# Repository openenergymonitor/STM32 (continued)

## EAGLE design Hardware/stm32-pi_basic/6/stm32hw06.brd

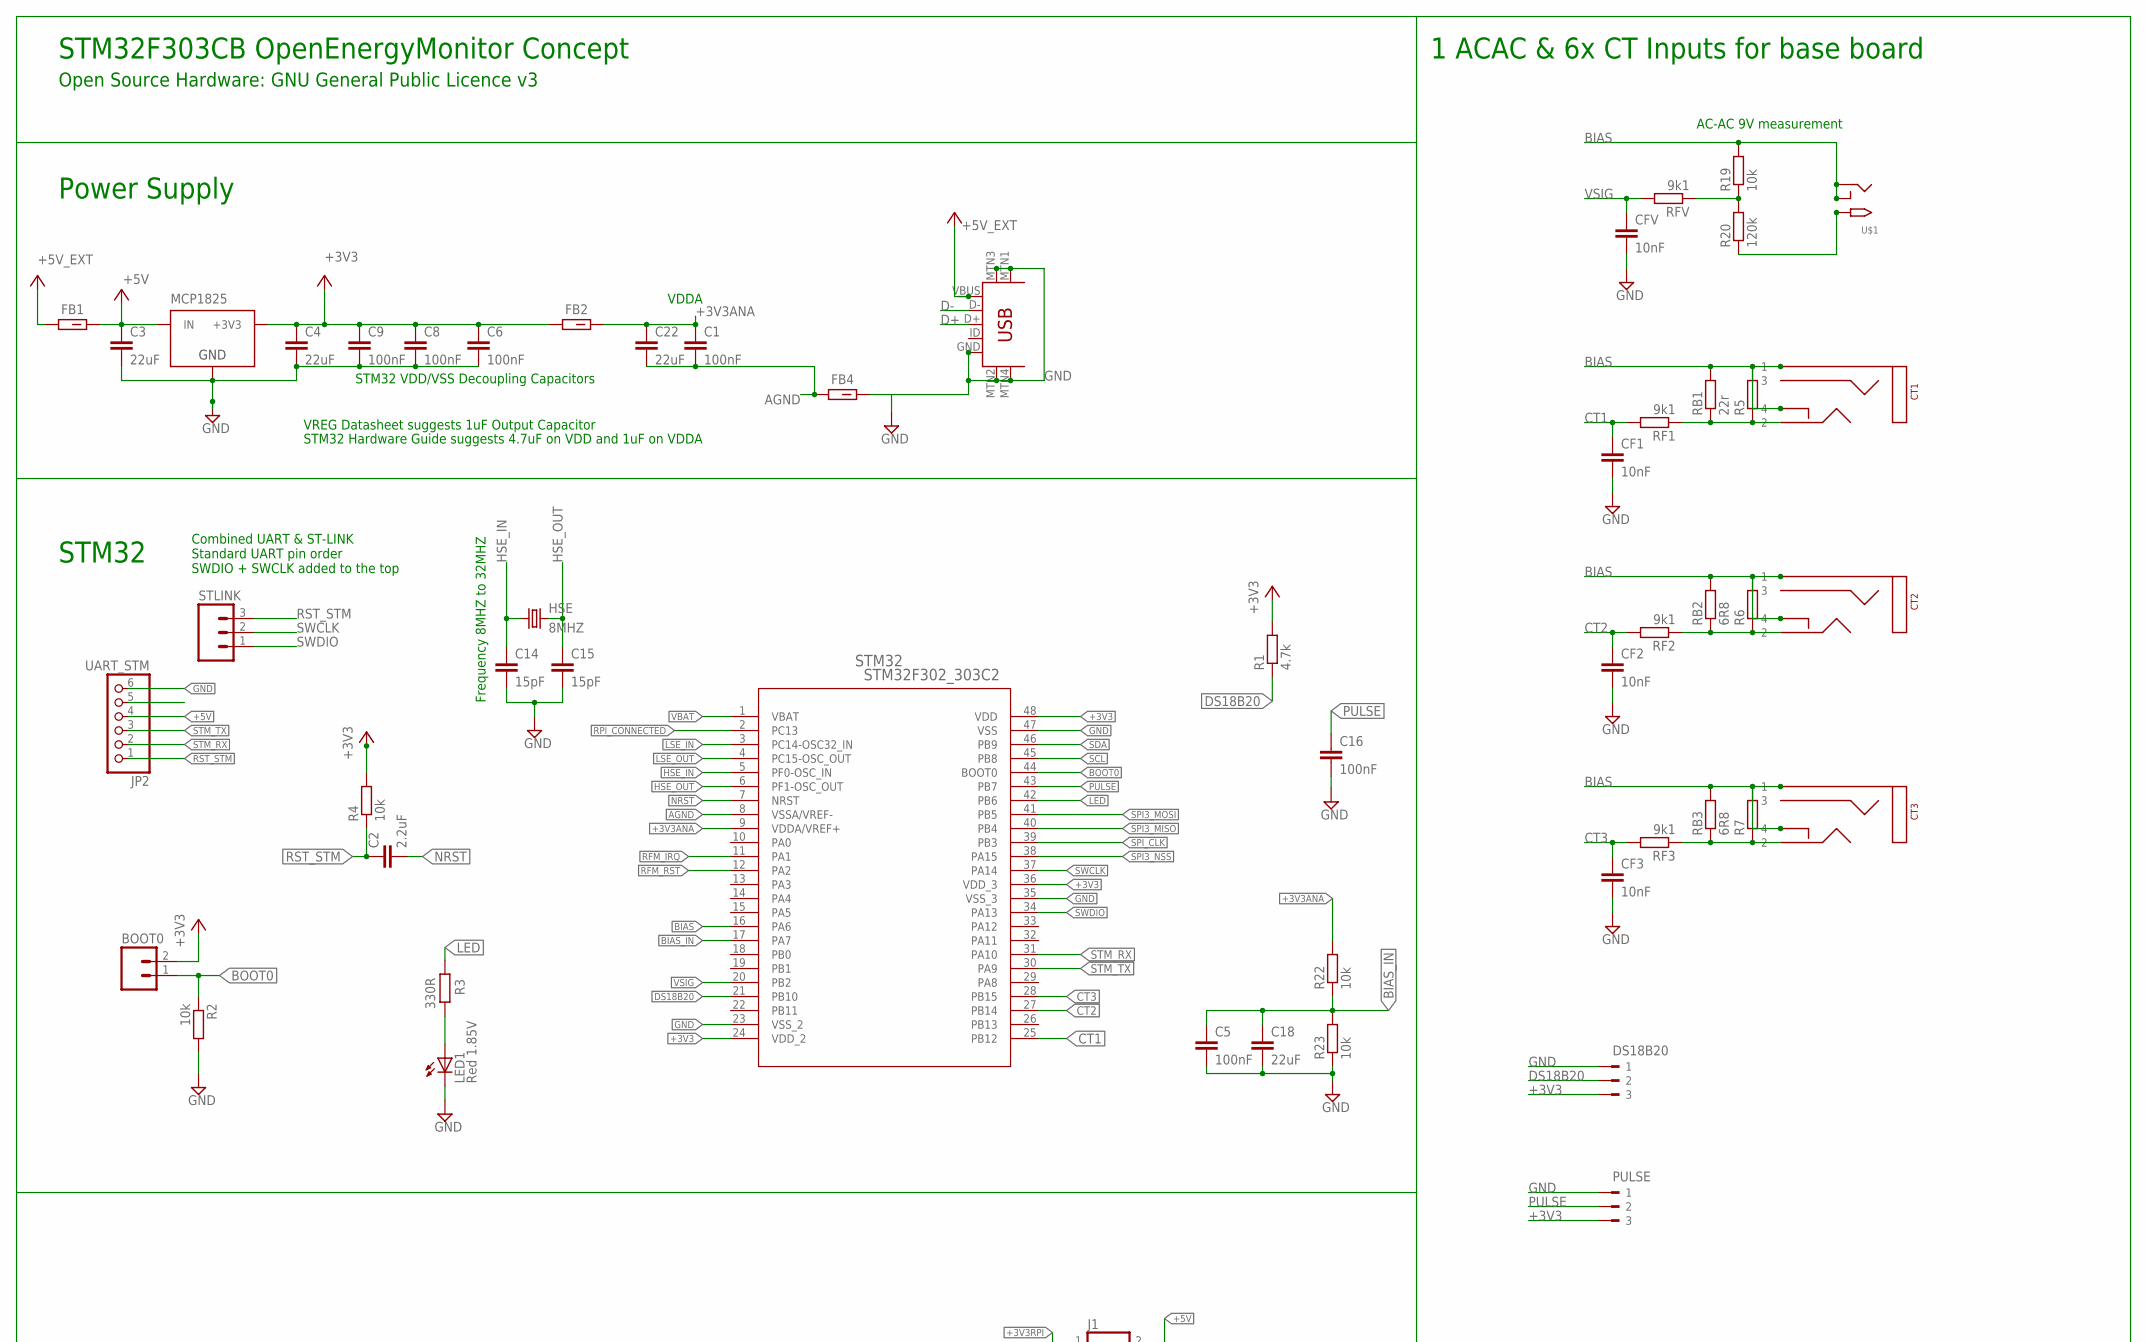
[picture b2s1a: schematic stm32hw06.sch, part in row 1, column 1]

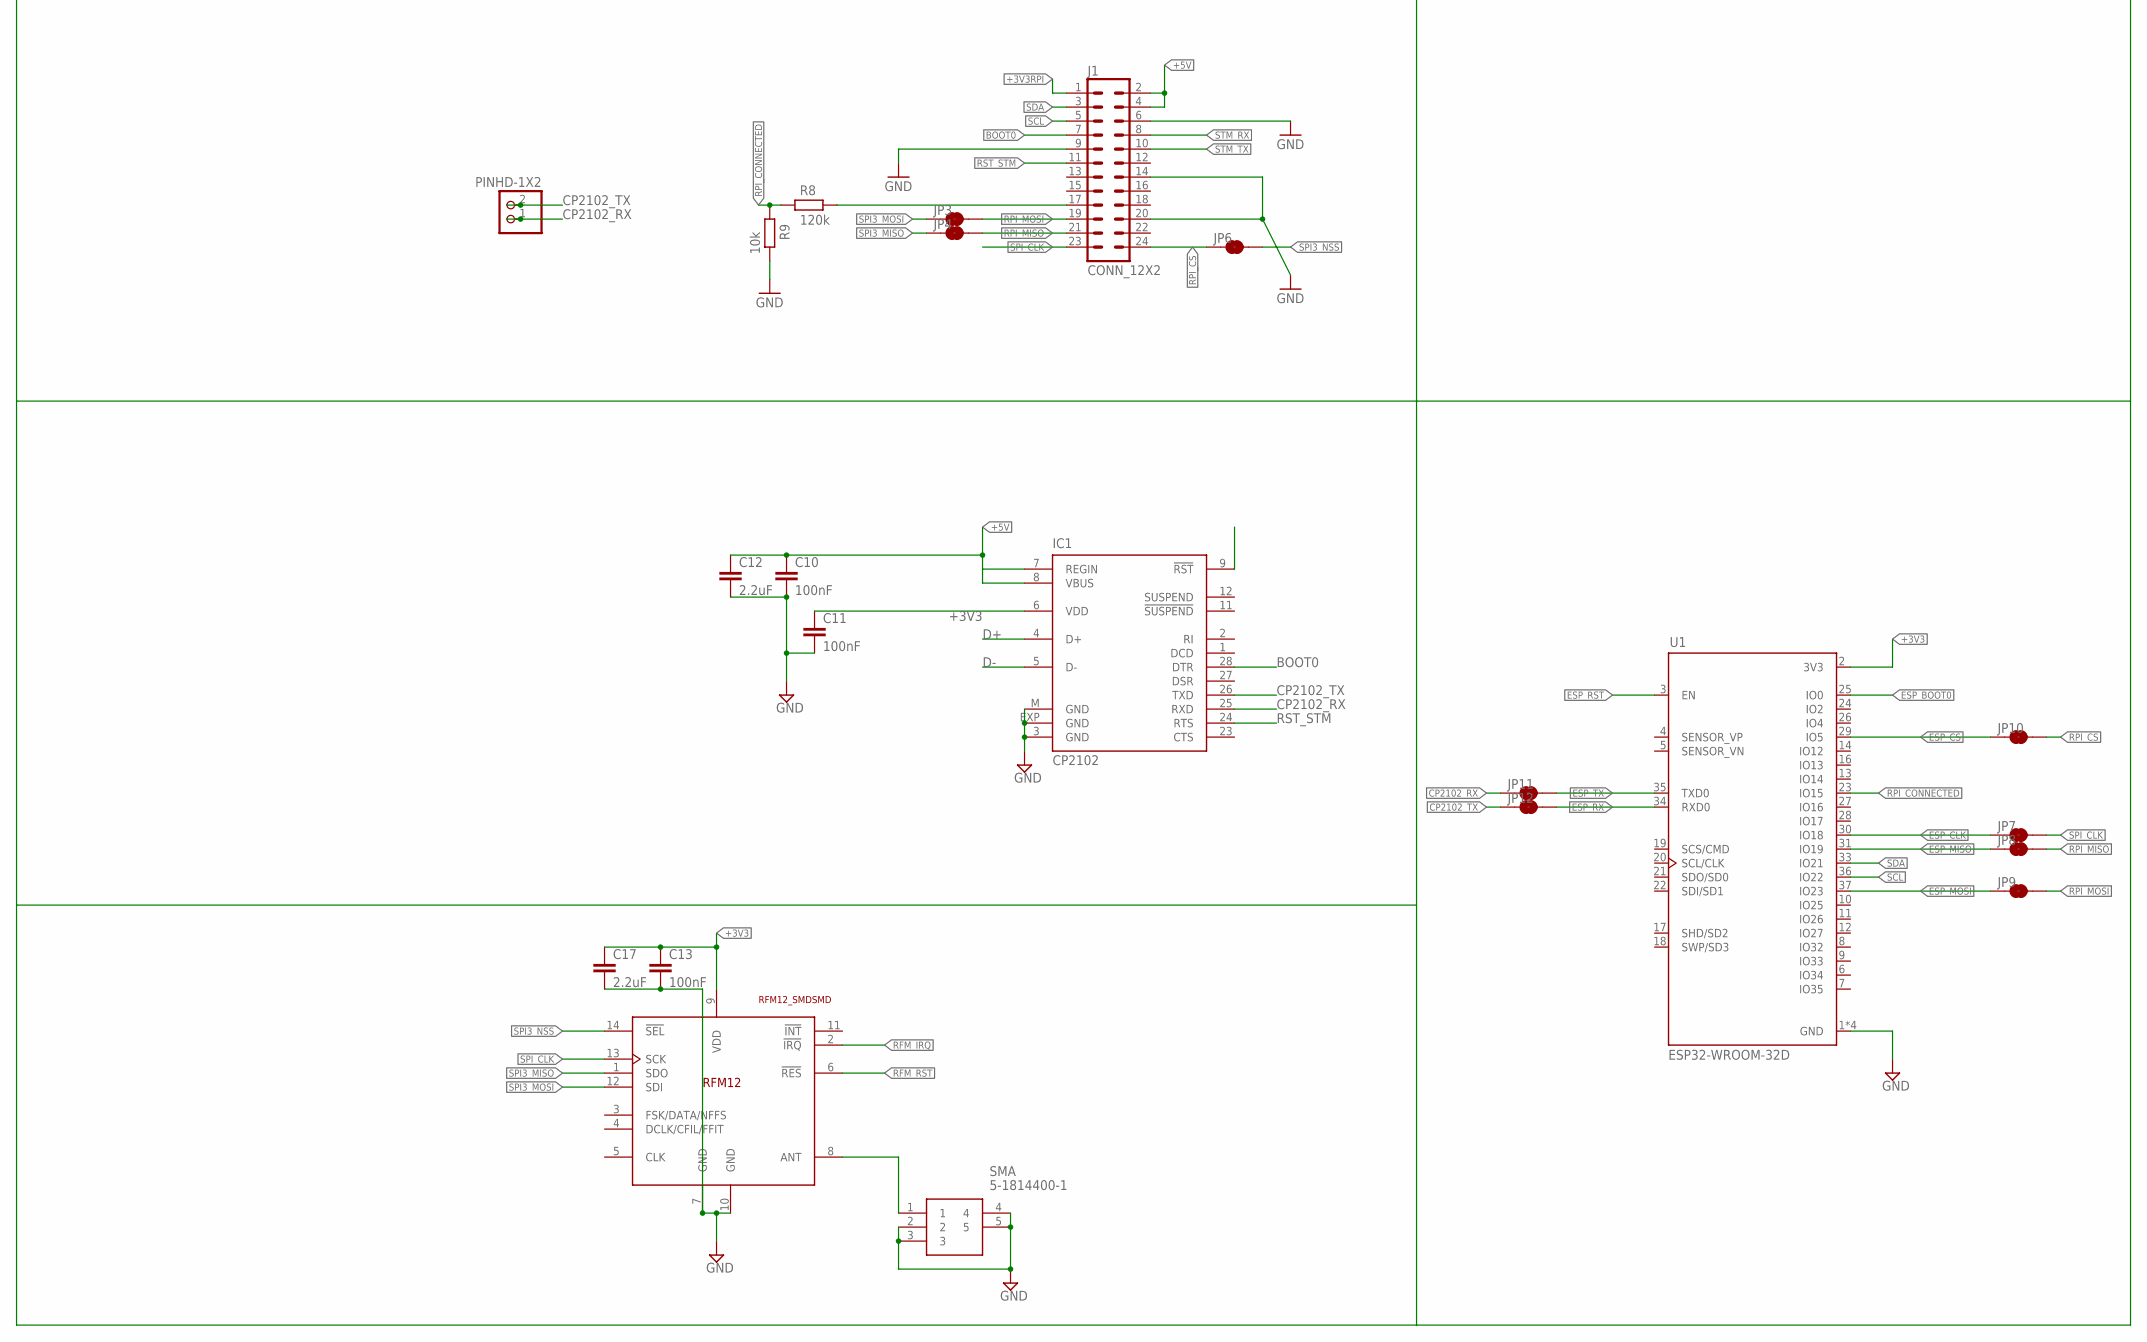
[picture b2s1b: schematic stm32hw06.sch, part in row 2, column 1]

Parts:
BOOT0: M02PTH; 1X02
C1, C5, C6, C8, C9, C10, C11, C13, C16: 100nF; C0603
C2, C12, C17: 2.2uF; C0603
C3, C4, C18, C22: 22uF; C0805
C14, C15: 15pF; C0603
CF1, CF2, CF3: 10nF; C0805
CFV: 10nF; C0805
CT1, CT2, CT3: STEREO_SMD; STEREO_SMT
DS18B20: 180-3
FB1, FB2, FB4: FBCHIP-0603(1608-METRIC); BEADC1608X95N
HSE: 8MHZ; CTS406
IC1: CP2102; MLP28
J1: CONN_12X2; 2X12
JP1: PINHD-1X2; 1X02
JP2: UART_STM; 1X06
JP3, JP4, JP6, JP7, JP8, JP9, JP10, JP11, JP12: JUMPER-SMT_2_NC_TRACE_NO-SILK; SMT-JUMPER_2_NC_TRACE_NO-SILK
LED1: Red 1.85V; CHIP-LED0805
MCP1825: MCP1825SOT-223-3; SOT-223
PULSE: 180-3
R1: 4.7k; R0603
R2, R4, R9, R19, R22, R23: 10k; R0603
R3: 330R; R0603
R5, R6, R7: R-EU_0207/10; 0207/10
R8, R20: 120k; R0603
RB1: 22r; R0603
RB2, RB3: 6R8; R0603
RF1, RF2, RF3: 9k1; R0603
RFV: 9k1; R0603
SMA: 5-1814400-1; 518144001
STLINK: M03PTH; 1X03
STM32: STM32F302_303C2; LQFP48-7X7MM
U1: ESP32-WROOM-32D; MODULE_ESP32-WROOM-32D
U$1: 2.1MMJACKSMT; DCJACK_2MM_SMT
U$2: RFM12_SMDSMD; RFM12
U$10: USB-MINIB-5PIN; USB-MINIB-CISECO

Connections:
+3V3: BOOT0.2, C4.1, C6.1, C8.1, C9.1, C11.1, C13.1, C17.1, DS18B20.3, FB2.1, IC1.6 (VDD), MCP1825.3 (+3V3), PULSE.3, R1.2, R4.2, STM32.24 (VDD_2), STM32.36 (VDD_3), STM32.48 (VDD), U1.2 (3V3), U$2.9 (VDD)
+3V3ANA: C1.1, C22.1, FB2.2, R22.2, STM32.9 (VDDA/VREF+)
+3V3RPI: J1.1
+5V: C3.1, C10.1, C12.1, FB1.2, IC1.7 (REGIN), IC1.8 (VBUS), J1.2, J1.4, JP2.4, MCP1825.1 (IN)
+5V_EXT: FB1.1, U$10.VBUS
AC: R20.1, U$1.PWR2 (TIP)
ADC0: R19.1, R20.2, RFV.1
AGND: C1.2, C22.2, FB4.1, STM32.8 (VSSA/VREF-)
BIAS: CT1.P$1 (1), CT1.P$4 (4), CT2.P$1 (1), CT2.P$4 (4), CT3.P$1 (1), CT3.P$4 (4), R5.2, R6.2, R7.2, R19.2, RB1.2, RB2.2, RB3.2, STM32.16 (PA6), U$1.GND (RING), U$1.GNDBREAK (RING_SW)
BIAS_IN: C5.1, C18.1, R22.1, R23.2, STM32.17 (PA7)
BOOT0: BOOT0.1, IC1.28 (DTR), J1.7, R2.1, STM32.44 (BOOT0)
CP2102_RX: IC1.25 (RXD), JP1.1, JP11.1
CP2102_TX: IC1.26 (TXD), JP1.2, JP12.1
CT1: CF1.1, RF1.2, STM32.25 (PB12)
CT2: CF2.1, RF2.2, STM32.27 (PB14)
CT3: CF3.1, RF3.2, STM32.28 (PB15)
D+: IC1.4 (D+), U$10.D+
D-: IC1.5 (D-), U$10.D-
DS18B20: DS18B20.2, R1.1, STM32.21 (PB10)
ESP_BOOT0: U1.25 (IO0)
ESP_CLK: JP7.1, U1.30 (IO18)
ESP_CS: JP10.1, U1.29 (IO5)
ESP_MISO: JP8.1, U1.31 (IO19)
ESP_MOSI: JP9.1, U1.37 (IO23)
ESP_RST: U1.3 (EN)
ESP_RX: JP12.2, U1.34 (RXD0)
ESP_TX: JP11.2, U1.35 (TXD0)
GND: C3.2, C4.2, C5.2, C6.2, C8.2, C9.2, C10.2, C11.2, C12.2, C13.2, C14.2, C15.2, C16.2, C17.2, C18.2, CF1.2, CF2.2, CF3.2, CFV.2, DS18B20.1, FB4.2, IC1.3 (GND), IC1.EXP (GND), IC1.M (GND), J1.6, J1.14, J1.20, JP2.6, LED1.C, MCP1825.2 (GND), PULSE.1, R2.2, R9.1, R23.1, SMA.2, SMA.3, SMA.4, SMA.5, STM32.23 (VSS_2), STM32.35 (VSS_3), STM32.47 (VSS), U1.1 (GND), U1.15 (GND), U1.38 (GND), U1.39 (GND), U$2.7 (GND), U$2.10 (GND), U$10.GND, U$10.MTN1 (MTN2), U$10.MTN2 (MTN3), U$10.MTN3 (MTN1), U$10.MTN4
HSE_IN: C14.1, HSE.1, STM32.5 (PF0-OSC_IN)
HSE_OUT: C15.1, HSE.3 (2), STM32.6 (PF1-OSC_OUT)
LED: R3.2, STM32.42 (PB6)
LSE_IN: STM32.3 (PC14-OSC32_IN)
LSE_OUT: STM32.4 (PC15-OSC_OUT)
unnamed: CT1.P$2 (2), R5.1, RB1.1, RF1.1
unnamed: CT2.P$2 (2), R6.1, RB2.1, RF2.1
unnamed: CT3.P$2 (2), R7.1, RB3.1, RF3.1
unnamed: SMA.1, U$2.8 (ANT)
unnamed: LED1.A, R3.1
NRST: C2.2, STM32.7 (NRST)
PULSE: C16.1, PULSE.2, STM32.43 (PB7)
RFM_IRQ: STM32.11 (PA1), U$2.2 (!IRQ)
RFM_RST: STM32.12 (PA2), U$2.6 (!RES)
RPI_CONNECTED: R8.2, R9.2, STM32.2 (PC13), U1.23 (IO15)
RPI_CONNECTED_PR: J1.17, R8.1
RPI_CS: J1.24, JP6.1, JP10.2
RPI_MISO: J1.21, JP4.2, JP8.2
RPI_MOSI: J1.19, JP3.2, JP9.2
RST_STM: C2.1, IC1.24 (RTS), J1.11, JP2.1, R4.1, STLINK.3
SCL: J1.5, STM32.45 (PB8), U1.36 (IO22)
SDA: J1.3, STM32.46 (PB9), U1.33 (IO21)
SPI3_MISO: JP4.1, STM32.40 (PB4), U$2.1 (SDO)
SPI3_MOSI: JP3.1, STM32.41 (PB5), U$2.12 (SDI)
SPI3_NSS: JP6.2, STM32.38 (PA15), U$2.14 (!SEL)
SPI_CLK: J1.23, JP7.2, STM32.39 (PB3), U$2.13 (SCK)
STM_RX: J1.8, JP2.2, STM32.31 (PA10)
STM_TX: J1.10, JP2.3, STM32.30 (PA9)
SWCLK: STLINK.2, STM32.37 (PA14)
SWDIO: STLINK.1, STM32.34 (PA13)
VBAT: STM32.1 (VBAT)
VSIG: CFV.1, RFV.2, STM32.20 (PB2)

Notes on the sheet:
STM32 VDD/VSS Decoupling Capacitors
VDDA
VREG Datasheet suggests 1uF Output Capacitor
STM32 Hardware Guide suggests 4.7uF on VDD and 1uF on VDDA
Combined UART & ST-LINK Standard UART pin order SWDIO + SWCLK added to the top
AC-AC 9V measurement
1 ACAC & 6x CT Inputs for base board
STM32F303CB OpenEnergyMonitor Concept
Power Supply
STM32
Open Source Hardware: GNU General Public Licence v3
Frequency 8MHZ to 32MHZ

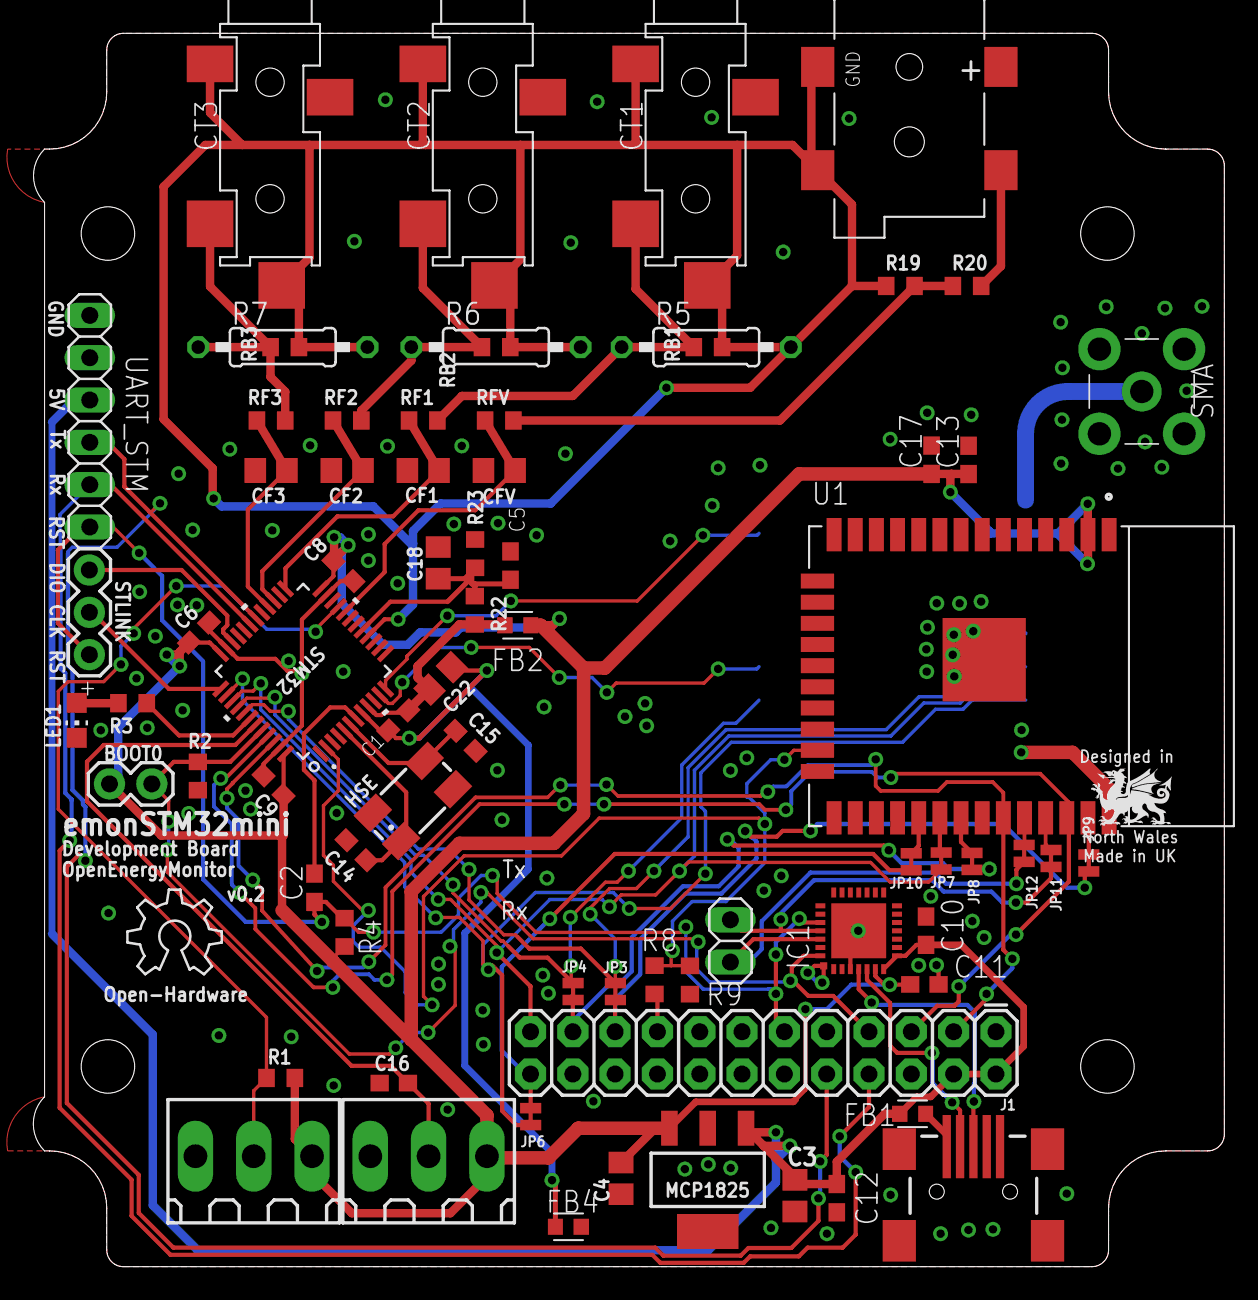
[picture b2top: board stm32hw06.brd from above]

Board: 2 copper layers, 71.5 x 74.0 mm, 75 parts (1 on the bottom side), 54 nets.

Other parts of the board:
LOGO1: OSHW_LOGO_6MILX0200-NT; OSHW_6X200_NOTEXT
